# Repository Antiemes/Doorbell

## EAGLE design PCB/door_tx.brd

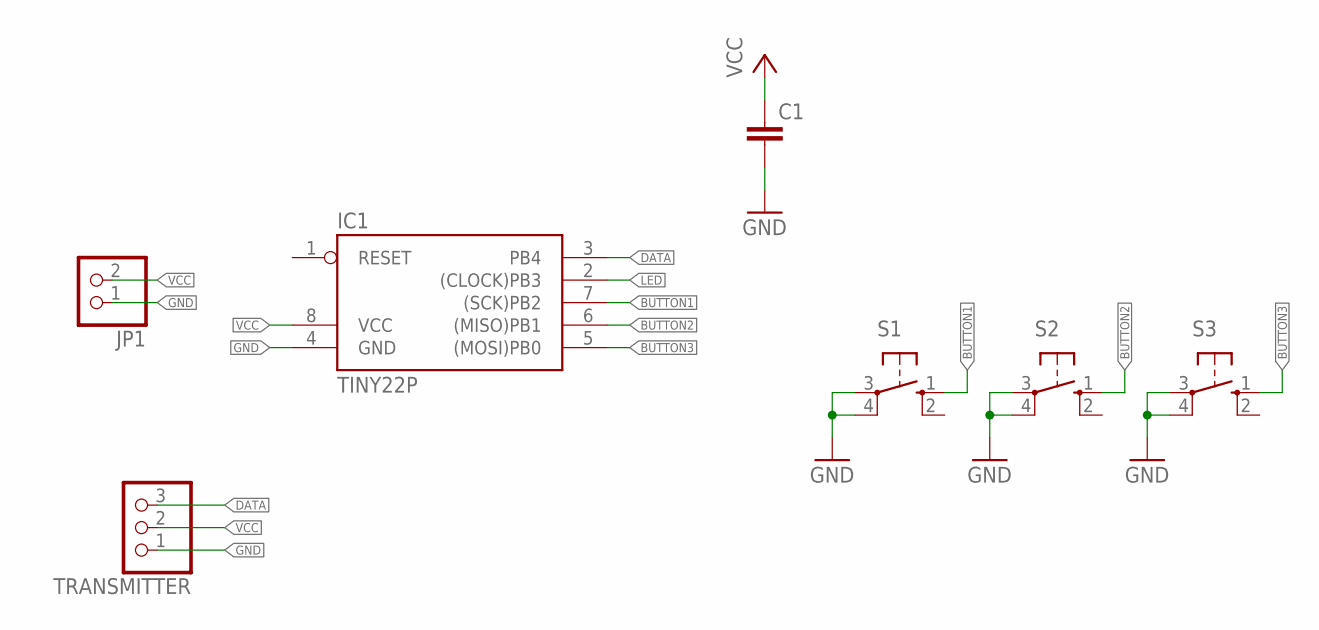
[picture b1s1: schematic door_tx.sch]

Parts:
C1: C-EUC1206K; C1206K
IC1: TINY22P; DIL08
JP1: PINHD-1X2; 1X02
S1, S2, S3: 10-XX; B3F-10XX
TRANSMITTER: PINHD-1X3; 1X03

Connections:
BUTTON1: IC1.7 ((SCK)PB2), S1.1 (S)
BUTTON2: IC1.6 ((MISO)PB1), S2.1 (S)
BUTTON3: IC1.5 ((MOSI)PB0), S3.1 (S)
DATA: IC1.3 (PB4), TRANSMITTER.3
GND: C1.2, IC1.4 (GND), JP1.1, S1.3, S1.4 (P1), S2.3, S2.4 (P1), S3.3, S3.4 (P1), TRANSMITTER.1
LED: IC1.2 ((CLOCK)PB3)
VCC: C1.1, IC1.8 (VCC), JP1.2, TRANSMITTER.2

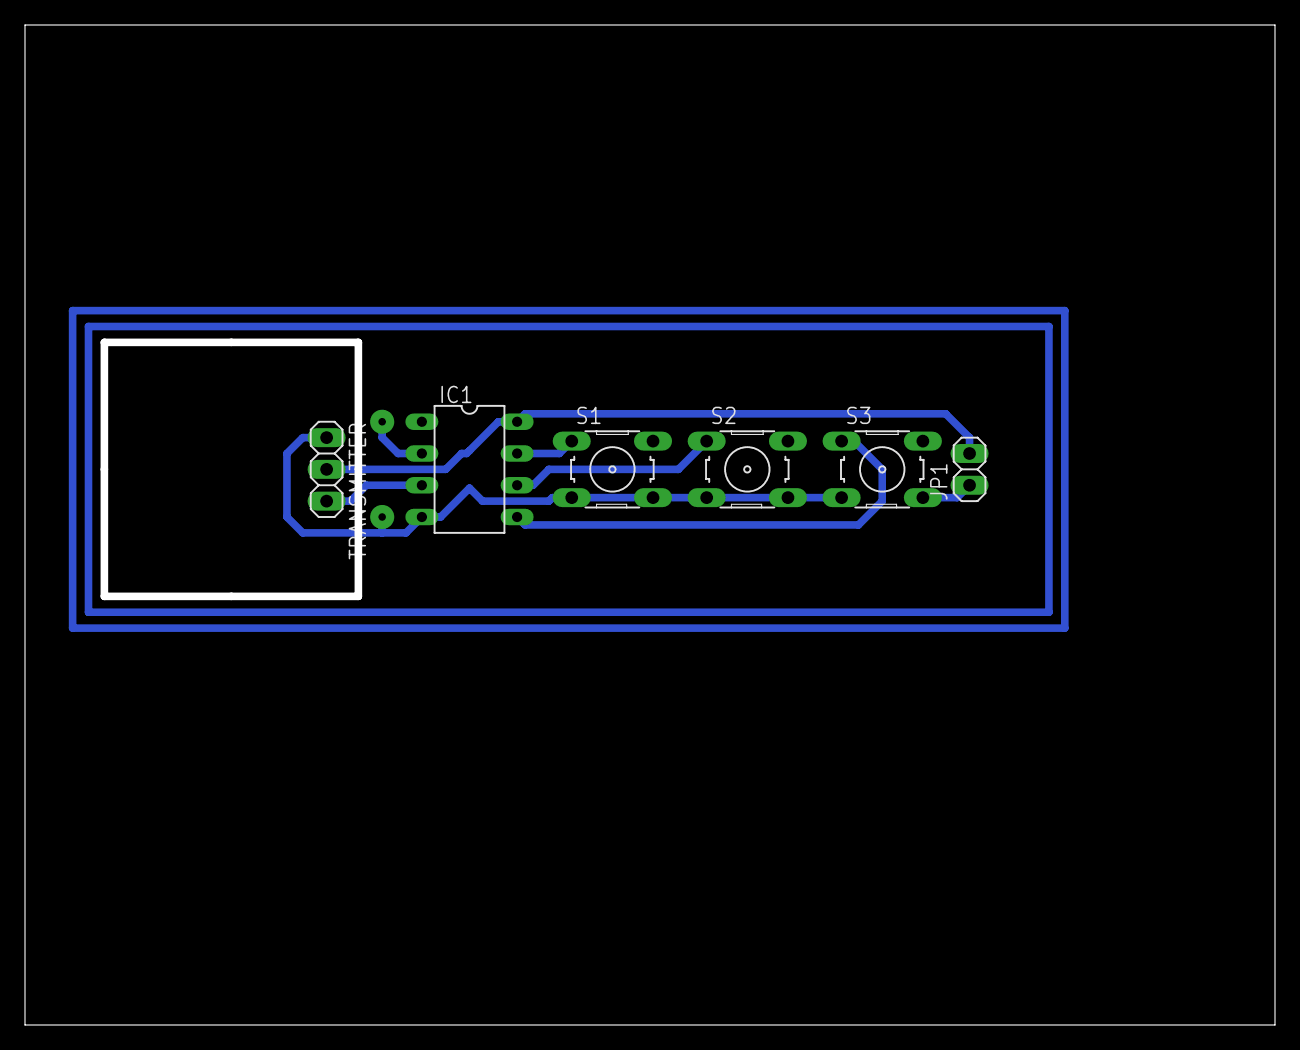
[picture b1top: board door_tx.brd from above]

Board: 2 copper layers, 99.4 x 79.4 mm, 7 parts (1 on the bottom side), 6 nets.

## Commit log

2020-04-19 Files copied from another repo.
2020-04-19 Chime code tested.
2020-07-13 PCB files added
2021-03-18 Code cleanup
